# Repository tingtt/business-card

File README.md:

# taku-ting's business cards

- [modu-tone](./modu-tone/): modu-tone PCB business card

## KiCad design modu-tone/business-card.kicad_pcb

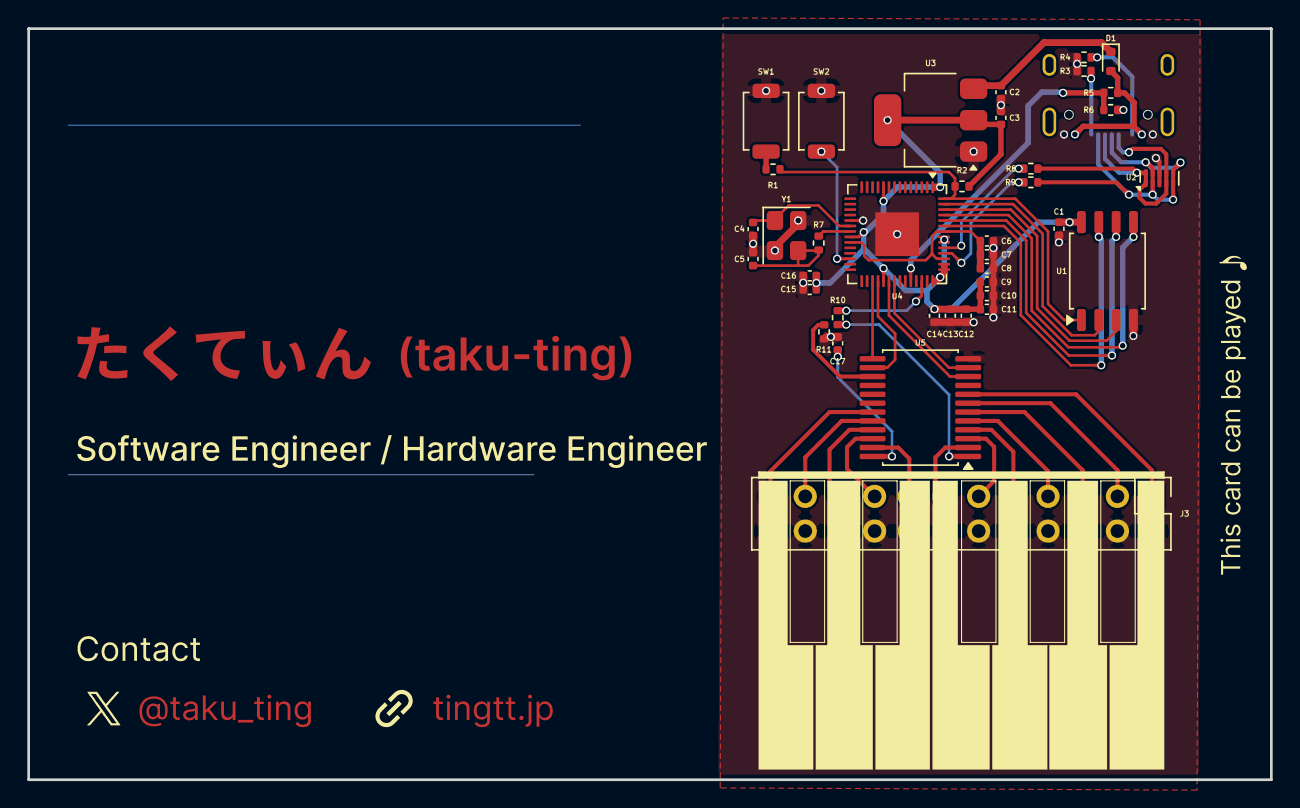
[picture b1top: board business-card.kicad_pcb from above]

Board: 2 copper layers, 91.0 x 55.0 mm, 39 parts (1 on the bottom side), 43 nets.

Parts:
C1, C7, C10: 1u; C_0402_1005Metric
C2, C3: 10u; C_0402_1005Metric
C4, C5: 27p; C_0402_1005Metric
C6, C8, C9, C11, C12, C13, C14, C15, C16, C17: 100n; C_0402_1005Metric
D1: RB521S30T1G; D_SOD-523
J1: USB_C_Receptacle_USB2.0_16P; USB_C_Receptacle_HRO_TYPE-C-31-M-12
J3: Conn_02x12; PinHeader_2x12_P2.54mm_Vertical
R1, R7: 1k; R_0402_1005Metric
R2, R11: 10k; R_0402_1005Metric
R3, R4: 5.1k; R_0402_1005Metric
R5: 5.6k; R_0402_1005Metric
R6: 10K; R_0402_1005Metric
R8, R9: 27; R_0402_1005Metric
R10: 100; R_0402_1005Metric
SW1, SW2: TS-1088R-020; SW_SPST_TS-1088-xR020
U1: W25Q128JVS; SOIC-8_5.3x5.3mm_P1.27mm
U2: TPD4E05U06DQAR; USON-10_2.5x1.0mm_P0.5mm
U3: NCP1117LPST33T3G; SOT-223-3_TabPin2
U4: RP2040; QFN-56-1EP_7x7mm_P0.4mm_EP3.2x3.2mm
U5: CD74HC4067PW; SSOP-24_5.3x8.2mm_P0.65mm
Y1: 12MHz 18pF; Crystal_SMD_3225-4Pin_3.2x2.5mm

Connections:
+1V1: C6.1, C7.1, C8.1, U4.23 (DVDD), U4.45 (VREG_VOUT), U4.50 (DVDD)
+3V3: C1.1, C3.1, C9.1, C10.1, C11.1, C12.1, C13.1, C14.1, C15.1, C16.1, R2.2, U1.8 (VCC), U3.2 (VO), U4.1 (IOVDD), U4.10 (IOVDD), U4.22 (IOVDD), U4.33 (IOVDD), U4.42 (IOVDD), U4.43 (ADC_AVDD), U4.44 (VREG_IN), U4.48 (USB_VDD), U4.49 (IOVDD)
+5V: C2.1, D1.1 (K), U3.3 (VI)
/Key scan ADC: R10.2, U4.40 (GPIO28_ADC2)
/Key scan MUX S0: U4.31 (GPIO20), U5.13 (S3)
/Key scan MUX S1: U4.32 (GPIO21), U5.14 (S2)
/Key scan MUX S2: U4.34 (GPIO22), U5.10 (S0)
/Key scan MUX S3: U4.35 (GPIO23), U5.11 (S1)
GND: C1.2, C2.2, C3.2, C4.2, C5.2, C6.2, C7.2, C8.2, C9.2, C10.2, C11.2, C12.2, C13.2, C14.2, C15.2, C16.2, C17.1, J1.A1 (GND), J1.A12 (GND), J1.B1 (GND), J1.B12 (GND), J3.2, J3.4, J3.6, J3.8, J3.10, J3.12, J3.14, J3.16, J3.18, J3.20, J3.22, J3.24, R3.1, R4.1, R6.2, R11.1, SW1.1, SW2.1, U1.4 (GND), U2.3 (GND), U2.8 (GND), U3.1 (GND), U4.19 (TESTEN), U4.57 (GND), U5.12 (GND), Y1.2, Y1.4
unnamed: C5.1, R7.1, Y1.3
unnamed: J1.A5 (CC1), R3.2
unnamed: J1.B5 (CC2), R4.2
unnamed: J3.1, U5.8 (I1)
unnamed: J3.3, U5.7 (I2)
unnamed: J3.5, U5.6 (I3)
unnamed: J3.7, U5.5 (I4)
unnamed: J3.9, U5.4 (I5)
unnamed: J3.11, U5.3 (I6)
unnamed: J3.13, U5.2 (I7)
unnamed: J3.15, U5.23 (I8)
unnamed: J3.17, U5.22 (I9)
unnamed: J3.19, U5.21 (I10)
unnamed: J3.21, U5.20 (I11)
unnamed: J3.23, U5.19 (I12)
unnamed: R1.2, SW1.2
unnamed: SW2.2, U4.26 (RUN)
unnamed: R9.1, U4.46 (USB_DM)
unnamed: R8.2, U4.47 (USB_DP)
unnamed: C4.1, U4.20 (XIN), Y1.1
unnamed: R7.2, U4.21 (XOUT)
unnamed: R10.1, U5.1 (COM)
unnamed: C17.2, U5.24 (VCC)
unnamed: R11.2, U5.15 (~E)
QSPI_SCLK: U1.6 (CLK), U4.52 (QSPI_SCLK)
QSPI_SD0: U1.5 (DI/IO_{0}), U4.53 (QSPI_SD0)
QSPI_SD1: U1.2 (DO/IO_{1}), U4.55 (QSPI_SD1)
QSPI_SD2: U1.3 (~WP/IO_{2}), U4.54 (QSPI_SD2)
QSPI_SD3: U1.7 (~HOLD/~RESET/IO_{3}), U4.51 (QSPI_SD3)
QSPI_SS: R1.1, R2.1, U1.1 (~CS), U4.56 (QSPI_SS)
USB_DP_D+: J1.A6 (D+), J1.B6 (D+), R8.1, U2.1 (D1+), U2.4 (D2+), U2.7 (NC), U2.10 (NC)
USB_DP_D-: J1.A7 (D-), J1.B7 (D-), R9.2, U2.2 (D1-), U2.5 (D2-), U2.6 (NC), U2.9 (NC)
USB_VBUS: R5.2, R6.1, U4.38 (GPIO26_ADC0)
VBUS: D1.2 (A), J1.A4 (VBUS), J1.A9 (VBUS), J1.B4 (VBUS), J1.B9 (VBUS), R5.1
